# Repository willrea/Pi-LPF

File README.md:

Low pass filter to use with RPi and WSPR

Bill of Materials:

Part Value       MPN

C1   0.1uF       12061C104JAT2A                     
C2   56pF        12061A560JAT2A                     
C3   150pF       12062A151JAT2A                     
C4   150pF       12062A151JAT2A                     
C5   56pF        12061A560JAT2A                     
D1               ESD8351XV2T1G                      
L1   300nH       0603HP-R30X_LU                     
L2   390nH       1206CS-391XGLB                     
L3   300nH       0603HP-R30X_LU                     
X1   BNC         5-1634503-1 

Note: Capacitors and Inductors chosen for 10M band use

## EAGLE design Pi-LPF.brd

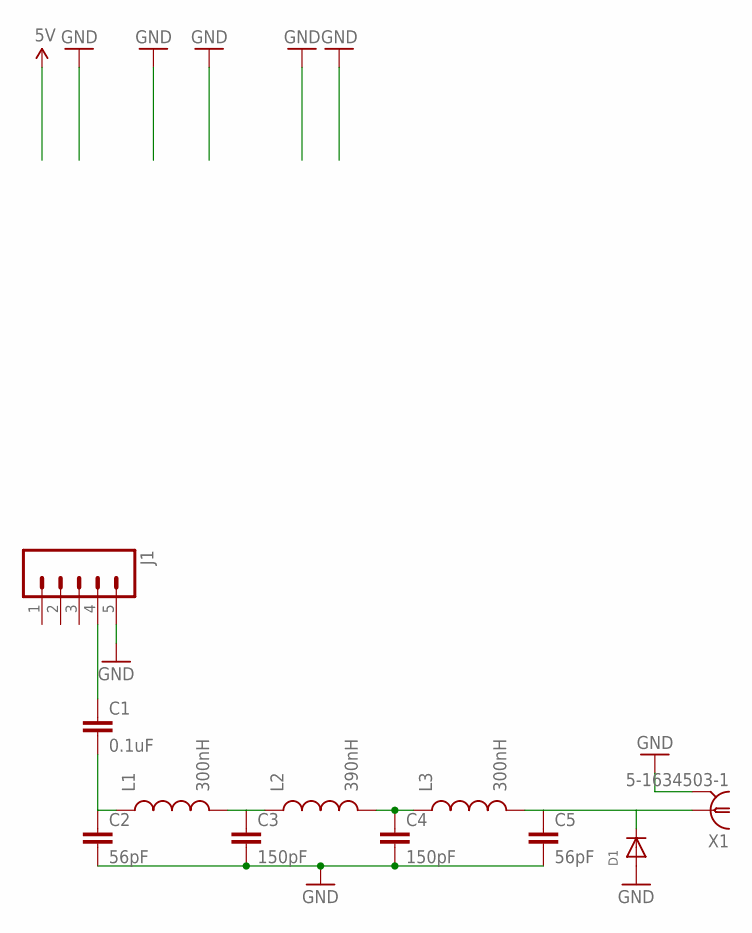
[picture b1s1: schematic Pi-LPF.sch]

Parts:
C1: 0.1uF; 1206; MPN 12061C104JAT2A
C2, C5: 56pF; 1206; MPN 12061A560JAT2A
C3, C4: 150pF; 1206; MPN 12062A151JAT2A
D1: 250mA/100V; SOD-523; MPN ESD8351XV2T1G
J1: M05PTH; 1X05
L1, L3: 300nH; 0603; MPN 0603HP-R30X_LU
L2: 390nH; INDUCTOR-1206; MPN 1206CS-391XGLB
X1: 5-1634503-1; B35N61

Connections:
GND: C2.2, C3.2, C4.2, C5.2, D1.A, J1.5, X1.2, X1.3 (2), X1.4 (2), X1.5 (2)
unnamed: C3.1, L1.2, L2.P$1 (1)
unnamed: C4.1, L2.P$2 (2), L3.1
unnamed: C1.2, C2.1, L1.1
unnamed: C5.1, D1.K (C), L3.2, X1.1
unnamed: C1.1, J1.4

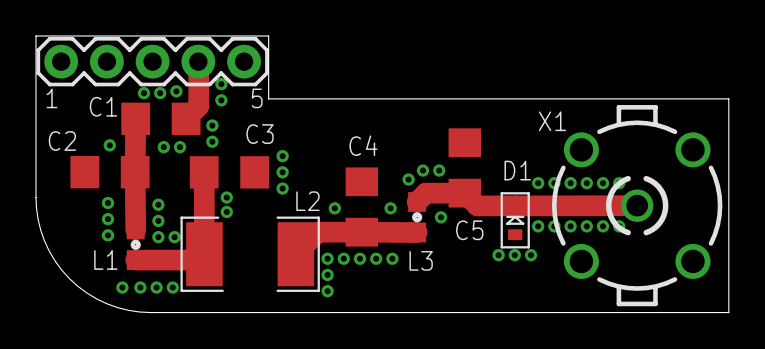
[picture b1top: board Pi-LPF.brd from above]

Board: 2 copper layers, 38.5 x 15.4 mm, 11 parts (0 on the bottom side), 6 nets.

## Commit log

2017-04-14 :octocat: Added .gitattributes & .gitignore files

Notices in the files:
parts and their libraries:
SparkFun-Capacitors: Licensing: Creative Commons ShareAlike 4.0 International - https://creativecommons.org/licenses/by-sa/4.0
